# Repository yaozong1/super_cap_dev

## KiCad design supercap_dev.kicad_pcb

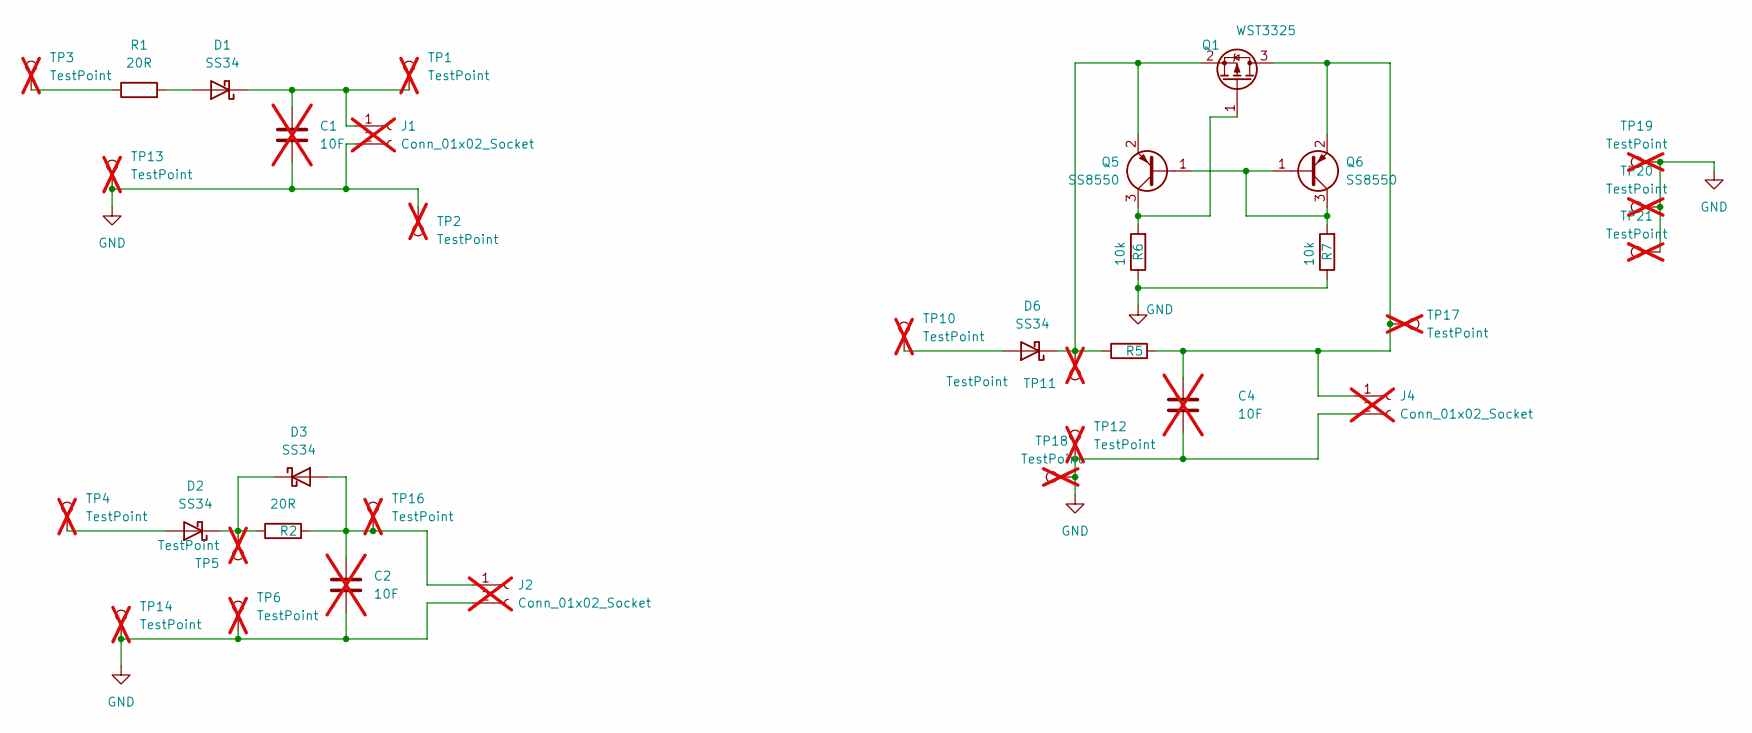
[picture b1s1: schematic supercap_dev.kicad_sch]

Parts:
C1, C2, C4: 10F; PinHeader_1x02_P2.54mm_Vertical; not fitted
D1, D2, D3, D6: SS34; D_SMA; LCSC Part C8678
J1, J2, J4: Conn_01x02_Socket; super_cap; not fitted
Q1: WST3325; SOT-23; MPN NTR3A30PZT1G; Digi-key PN NTR3A30PZT1GOSCT-ND
Q5, Q6: SS8550; SOT-23; LCSC Part C7420371
R1, R2, R5: 20R; R_0805_2012Metric; LCSC Part C17544
R6, R7: 10k; R_0603_1608Metric; LCSC Part C84376
TP1, TP2, TP3, TP4, TP5, TP6, TP10, TP11, TP12, TP13, TP14, TP16, TP17, TP18, TP19, TP20, TP21: TestPoint; TestPoint_Pad_D1.5mm; not fitted

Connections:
GND: C1.2, C2.2, C4.2, J1.2, J2.2, J4.2, R6.1, R7.1, TP2.1 (1_1), TP6.1 (1_1), TP12.1 (1_1), TP13.1 (1_1), TP14.1 (1_1), TP18.1 (1_1), TP19.1 (1_1), TP20.1 (1_1), TP21.1 (1_1)
unnamed: D1.2 (A), R1.2
unnamed: C1.1, D1.1 (K), J1.1, TP1.1 (1_1)
unnamed: D2.2 (A), TP4.1 (1_1)
unnamed: D2.1 (K), D3.1 (K), R2.1, TP5.1 (1_1)
unnamed: C2.1, D3.2 (A), J2.1, R2.2, TP16.1 (1_1)
unnamed: D6.2 (A), TP10.1 (1_1)
unnamed: D6.1 (K), Q1.2 (S), Q5.2 (E), R5.1, TP11.1 (1_1)
unnamed: C4.1, J4.1, Q1.3 (D), Q6.2 (E), R5.2, TP17.1 (1_1)
unnamed: Q1.1 (G), Q5.3 (C), R6.2
unnamed: Q5.1 (B), Q6.1 (B), Q6.3 (C), R7.2
unnamed: R1.1, TP3.1 (1_1)

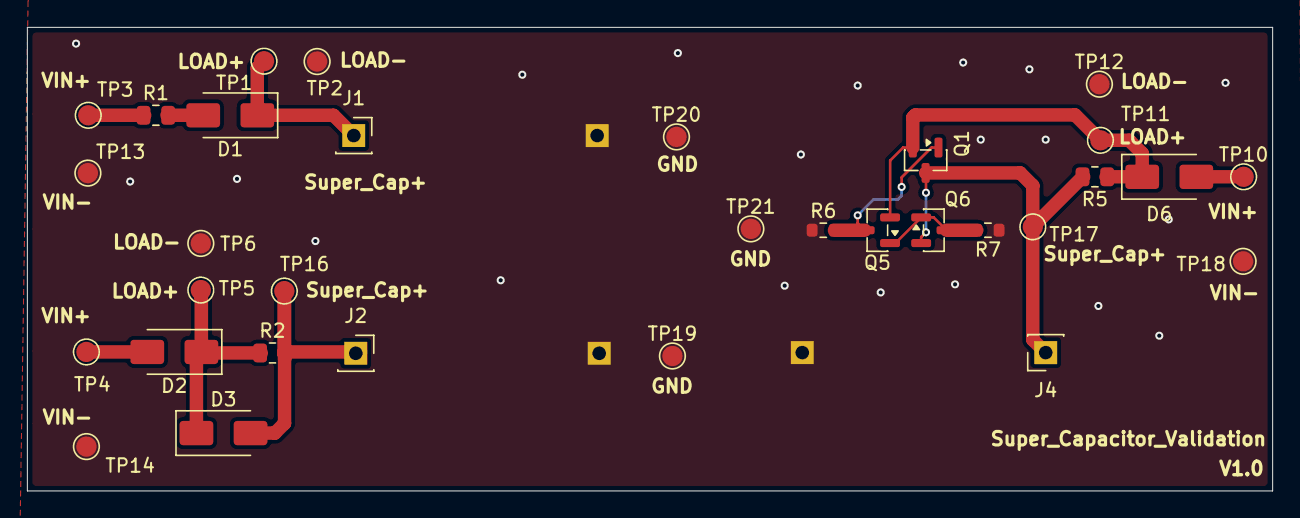
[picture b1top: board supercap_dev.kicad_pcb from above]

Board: 2 copper layers, 92.1 x 34.3 mm, 32 parts (0 on the bottom side), 12 nets.

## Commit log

2026-04-21 almost done
2026-04-21 Done
2026-04-21 saved
